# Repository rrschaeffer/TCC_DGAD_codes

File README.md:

# TCC_DGAD_codes
Repositório dos códigos utilizados - TCC Rafael R. Schaeffer - 2026/1

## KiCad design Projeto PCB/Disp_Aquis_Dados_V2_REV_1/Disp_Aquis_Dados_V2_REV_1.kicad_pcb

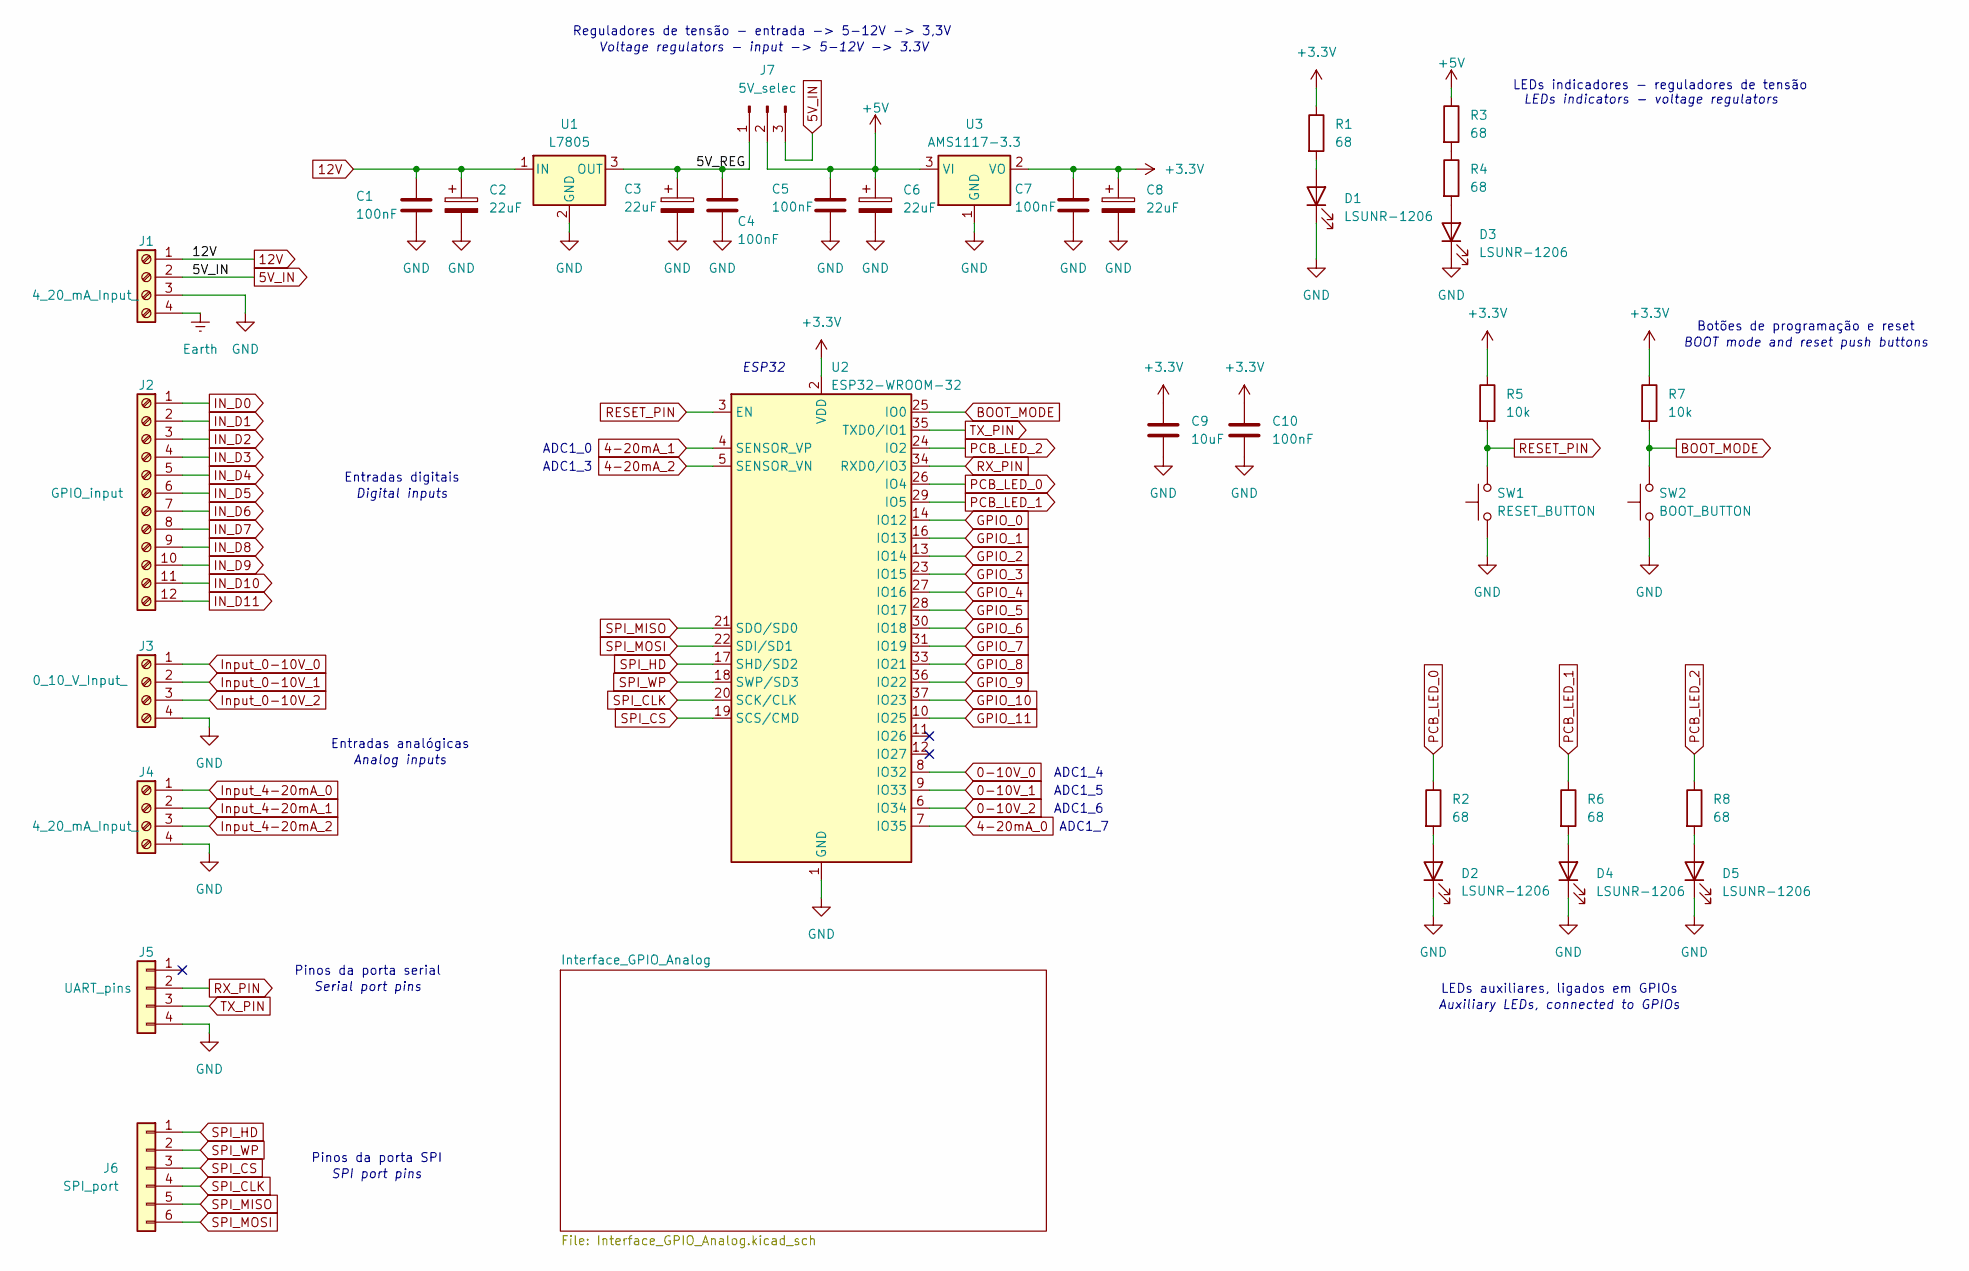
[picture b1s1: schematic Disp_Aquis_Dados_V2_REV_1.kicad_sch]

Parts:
C1, C4, C5, C7, C10: 100nF; C_0805_2012Metric_Pad1.18x1.45mm_HandSolder
C2, C3, C6, C8: 22uF; CP_Elec_5x5.3
C9: 10uF; C_0805_2012Metric_Pad1.18x1.45mm_HandSolder
D1, D2, D3, D4, D5: LSUNR-1206; LED_1206_3216Metric_Pad1.42x1.75mm_HandSolder
J1, J4: 4_20_mA_Input_; TerminalBlock_Phoenix_MKDS-1,5-4_1x04_P5.00mm_Horizontal
J2: GPIO_input; TerminalBlock_Phoenix_MKDS-1,5-12_1x12_P5.00mm_Horizontal
J3: 0_10_V_Input_; TerminalBlock_Phoenix_MKDS-1,5-4_1x04_P5.00mm_Horizontal
J5: UART_pins; PinHeader_1x04_P2.54mm_Vertical
J6: SPI_port; PinHeader_1x06_P2.54mm_Vertical
J7: 5V_selec; PinHeader_1x03_P2.54mm_Vertical
R1, R2, R3, R4, R6, R8: 68; R_1206_3216Metric_Pad1.30x1.75mm_HandSolder
R5, R7: 10k; R_1206_3216Metric_Pad1.30x1.75mm_HandSolder
SW1: RESET_BUTTON; SW_Push_1P1T_NO_6x6mm_H9.5mm
SW2: BOOT_BUTTON; SW_Push_1P1T_NO_6x6mm_H9.5mm
U1: L7805; TO-252-3_TabPin2
U2: ESP32-WROOM-32
U3: AMS1117-3.3; SOT-223

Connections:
0-10V_0: U2.8 (IO32); also elsewhere on the board
0-10V_1: U2.9 (IO33); also elsewhere on the board
0-10V_2: U2.6 (IO34); also elsewhere on the board
4-20mA_0: U2.7 (IO35); also elsewhere on the board
4-20mA_1: U2.4 (SENSOR_VP); also elsewhere on the board
4-20mA_2: U2.5 (SENSOR_VN); also elsewhere on the board
5V_IN: J1.2, J7.3
12V: C1.1, C2.1, J1.1, U1.1 (IN)
+3.3V: C7.1, C8.1, C9.1, C10.1, R1.1, R5.1, R7.1, U2.2 (VDD), U3.2 (VO); also elsewhere on the board
+5V: C5.1, C6.1, J7.2, R3.1, U3.3 (VI); also elsewhere on the board
/5V_REG: C3.1, C4.1, J7.1, U1.3 (OUT)
BOOT_MODE: R7.2, SW2.2, U2.25 (IO0)
Earth: J1.4
GND: C1.2, C2.2, C3.2, C4.2, C5.2, C6.2, C7.2, C8.2, C9.2, C10.2, D1.1 (K), D2.1 (K), D3.1 (K), D4.1 (K), D5.1 (K), J1.3, J3.4, J4.4, J5.4, SW1.1, SW2.1, U1.2 (GND), U2.1 (GND), U2.15 (GND), U2.38 (GND), U2.39 (GND), U3.1 (GND); also elsewhere on the board
GPIO_0: U2.14 (IO12); also elsewhere on the board
GPIO_1: U2.16 (IO13); also elsewhere on the board
GPIO_2: U2.13 (IO14); also elsewhere on the board
GPIO_3: U2.23 (IO15); also elsewhere on the board
GPIO_4: U2.27 (IO16); also elsewhere on the board
GPIO_5: U2.28 (IO17); also elsewhere on the board
GPIO_6: U2.30 (IO18); also elsewhere on the board
GPIO_7: U2.31 (IO19); also elsewhere on the board
GPIO_8: U2.33 (IO21); also elsewhere on the board
GPIO_9: U2.36 (IO22); also elsewhere on the board
GPIO_10: U2.37 (IO23); also elsewhere on the board
GPIO_11: U2.10 (IO25); also elsewhere on the board
IN_D0: J2.1; also elsewhere on the board
IN_D1: J2.2; also elsewhere on the board
IN_D2: J2.3; also elsewhere on the board
IN_D3: J2.4; also elsewhere on the board
IN_D4: J2.5; also elsewhere on the board
IN_D5: J2.6; also elsewhere on the board
IN_D6: J2.7; also elsewhere on the board
IN_D7: J2.8; also elsewhere on the board
IN_D8: J2.9; also elsewhere on the board
IN_D9: J2.10; also elsewhere on the board
IN_D10: J2.11; also elsewhere on the board
IN_D11: J2.12; also elsewhere on the board
Input_0-10V_0: J3.1; also elsewhere on the board
Input_0-10V_1: J3.2; also elsewhere on the board
Input_0-10V_2: J3.3; also elsewhere on the board
Input_4-20mA_0: J4.1; also elsewhere on the board
Input_4-20mA_1: J4.2; also elsewhere on the board
Input_4-20mA_2: J4.3; also elsewhere on the board
unnamed: D1.2 (A), R1.2
unnamed: D2.2 (A), R2.2
unnamed: D3.2 (A), R4.2
unnamed: D4.2 (A), R6.2
unnamed: D5.2 (A), R8.2
unnamed: R3.2, R4.1
PCB_LED_0: R2.1, U2.26 (IO4)
PCB_LED_1: R6.1, U2.29 (IO5)
PCB_LED_2: R8.1, U2.24 (IO2)
RESET_PIN: R5.2, SW1.2, U2.3 (EN)
RX_PIN: J5.2, U2.34 (RXD0/IO3)
SPI_CLK: J6.4, U2.20 (SCK/CLK)
SPI_CS: J6.3, U2.19 (SCS/CMD)
SPI_HD: J6.1, U2.17 (SHD/SD2)
SPI_MISO: J6.5, U2.21 (SDO/SD0)
SPI_MOSI: J6.6, U2.22 (SDI/SD1)
SPI_WP: J6.2, U2.18 (SWP/SD3)
TX_PIN: J5.3, U2.35 (TXD0/IO1)

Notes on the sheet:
LEDs indicators - voltage regulators
Pinos da porta serial
LEDs auxiliares, ligados em GPIOs
SPI port pins
Pinos da porta SPI
ADC1_7
ADC1_0
Digital inputs
ADC1_3
Auxiliary LEDs, connected to GPIOs
Entradas digitais
Voltage regulators - input -> 5-12V -> 3.3V
BOOT mode and reset push buttons
ESP32
Botões de programação e reset
ADC1_5
Analog inputs
ADC1_6
ADC1_4
Serial port pins
Reguladores de tensão - entrada -> 5-12V -> 3,3V
Entradas analógicas
LEDs indicadores - reguladores de tensão

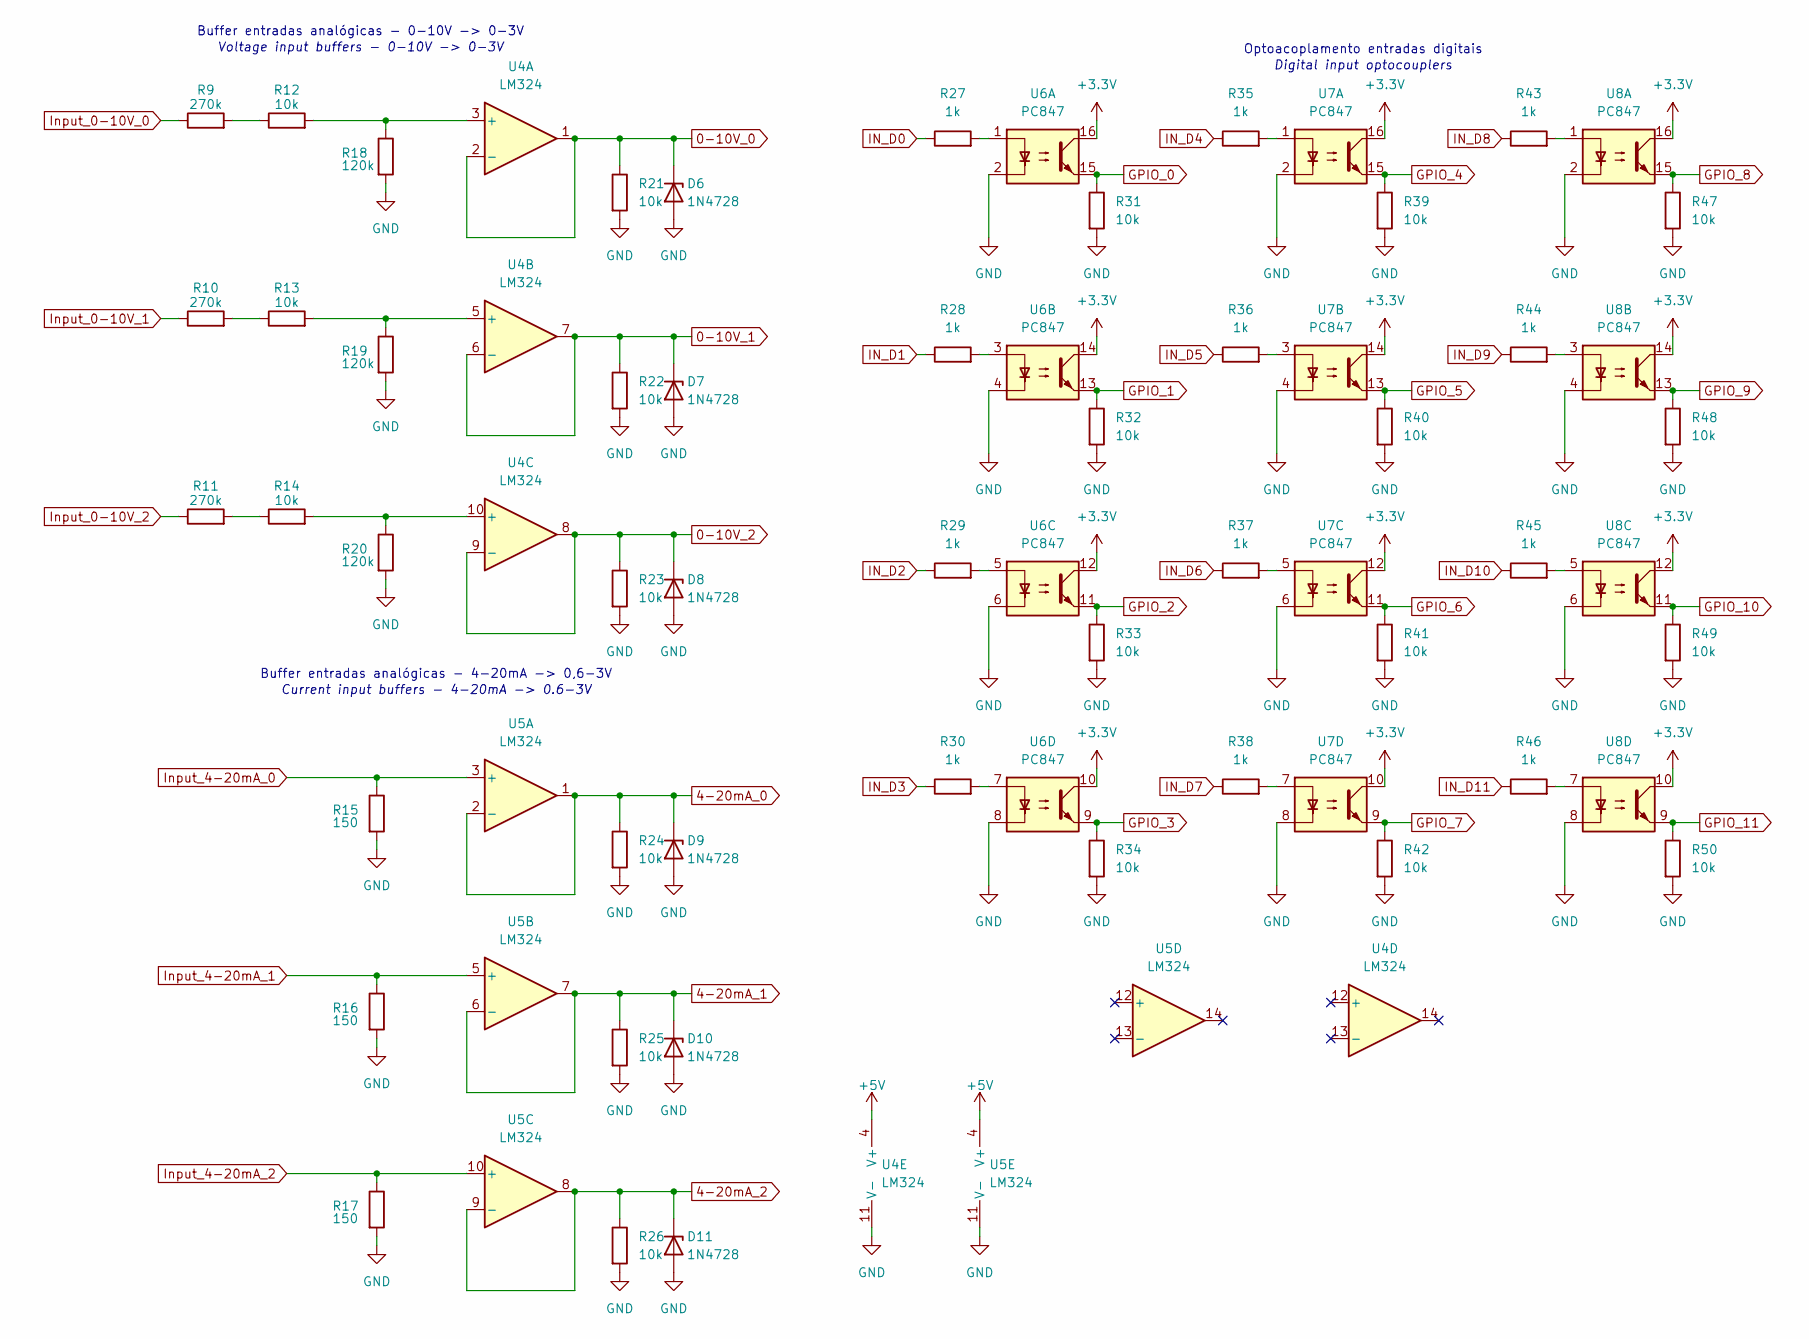
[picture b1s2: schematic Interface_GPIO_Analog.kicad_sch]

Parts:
D6, D7, D8, D9, D10, D11: 1N4728; D_DO-41_SOD81_P10.16mm_Horizontal
R9, R10, R11: 270k; R_1206_3216Metric_Pad1.30x1.75mm_HandSolder
R12, R13, R14, R21, R22, R23, R24, R25, R26, R31, R32, R33, R34, R39, R40, R41, R42, R47, R48, R49, R50: 10k; R_1206_3216Metric_Pad1.30x1.75mm_HandSolder
R15, R16, R17: 150; R_1206_3216Metric_Pad1.30x1.75mm_HandSolder
R18, R19, R20: 120k; R_1206_3216Metric_Pad1.30x1.75mm_HandSolder
R27, R28, R29, R30, R35, R36, R37, R38, R43, R44, R45, R46: 1k; R_2512_6332Metric_Pad1.40x3.35mm_HandSolder
U4, U5: LM324; SOIC-14_3.9x8.7mm_P1.27mm
U6, U7, U8: PC847; DIP-16_W7.62mm_Socket_LongPads

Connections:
0-10V_0: D6.1 (K), R21.1, U4.1, U4.2 (-); also elsewhere on the board
0-10V_1: D7.1 (K), R22.1, U4.6 (-), U4.7; also elsewhere on the board
0-10V_2: D8.1 (K), R23.1, U4.8, U4.9 (-); also elsewhere on the board
4-20mA_0: D9.1 (K), R24.1, U5.1, U5.2 (-); also elsewhere on the board
4-20mA_1: D10.1 (K), R25.1, U5.6 (-), U5.7; also elsewhere on the board
4-20mA_2: D11.1 (K), R26.1, U5.8, U5.9 (-); also elsewhere on the board
+3.3V: U6.10, U6.12, U6.14, U6.16, U7.10, U7.12, U7.14, U7.16, U8.10, U8.12, U8.14, U8.16; also elsewhere on the board
+5V: U4.4 (V+), U5.4 (V+); also elsewhere on the board
GND: D6.2 (A), D7.2 (A), D8.2 (A), D9.2 (A), D10.2 (A), D11.2 (A), R15.2, R16.2, R17.2, R18.2, R19.2, R20.2, R21.2, R22.2, R23.2, R24.2, R25.2, R26.2, R31.2, R32.2, R33.2, R34.2, R39.2, R40.2, R41.2, R42.2, R47.2, R48.2, R49.2, R50.2, U4.11 (V-), U5.11 (V-), U6.2, U6.4, U6.6, U6.8, U7.2, U7.4, U7.6, U7.8, U8.2, U8.4, U8.6, U8.8; also elsewhere on the board
GPIO_0: R31.1, U6.15; also elsewhere on the board
GPIO_1: R32.1, U6.13; also elsewhere on the board
GPIO_2: R33.1, U6.11; also elsewhere on the board
GPIO_3: R34.1, U6.9; also elsewhere on the board
GPIO_4: R39.1, U7.15; also elsewhere on the board
GPIO_5: R40.1, U7.13; also elsewhere on the board
GPIO_6: R41.1, U7.11; also elsewhere on the board
GPIO_7: R42.1, U7.9; also elsewhere on the board
GPIO_8: R47.1, U8.15; also elsewhere on the board
GPIO_9: R48.1, U8.13; also elsewhere on the board
GPIO_10: R49.1, U8.11; also elsewhere on the board
GPIO_11: R50.1, U8.9; also elsewhere on the board
IN_D0: R27.1; also elsewhere on the board
IN_D1: R28.1; also elsewhere on the board
IN_D2: R29.1; also elsewhere on the board
IN_D3: R30.1; also elsewhere on the board
IN_D4: R35.1; also elsewhere on the board
IN_D5: R36.1; also elsewhere on the board
IN_D6: R37.1; also elsewhere on the board
IN_D7: R38.1; also elsewhere on the board
IN_D8: R43.1; also elsewhere on the board
IN_D9: R44.1; also elsewhere on the board
IN_D10: R45.1; also elsewhere on the board
IN_D11: R46.1; also elsewhere on the board
Input_0-10V_0: R9.1; also elsewhere on the board
Input_0-10V_1: R10.1; also elsewhere on the board
Input_0-10V_2: R11.1; also elsewhere on the board
Input_4-20mA_0: R15.1, U5.3 (+); also elsewhere on the board
Input_4-20mA_1: R16.1, U5.5 (+); also elsewhere on the board
Input_4-20mA_2: R17.1, U5.10 (+); also elsewhere on the board
unnamed: R10.2, R13.1
unnamed: R11.2, R14.1
unnamed: R9.2, R12.1
unnamed: R27.2, U6.1
unnamed: R28.2, U6.3
unnamed: R29.2, U6.5
unnamed: R30.2, U6.7
unnamed: R35.2, U7.1
unnamed: R36.2, U7.3
unnamed: R37.2, U7.5
unnamed: R38.2, U7.7
unnamed: R43.2, U8.1
unnamed: R44.2, U8.3
unnamed: R45.2, U8.5
unnamed: R46.2, U8.7
unnamed: R12.2, R18.1, U4.3 (+)
unnamed: R13.2, R19.1, U4.5 (+)
unnamed: R14.2, R20.1, U4.10 (+)

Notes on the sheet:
Voltage input buffers - 0-10V -> 0-3V
Buffer entradas analógicas - 4-20mA -> 0,6-3V
Current input buffers - 4-20mA -> 0.6-3V
Digital input optocouplers
Optoacoplamento entradas digitais
Buffer entradas analógicas - 0-10V -> 0-3V

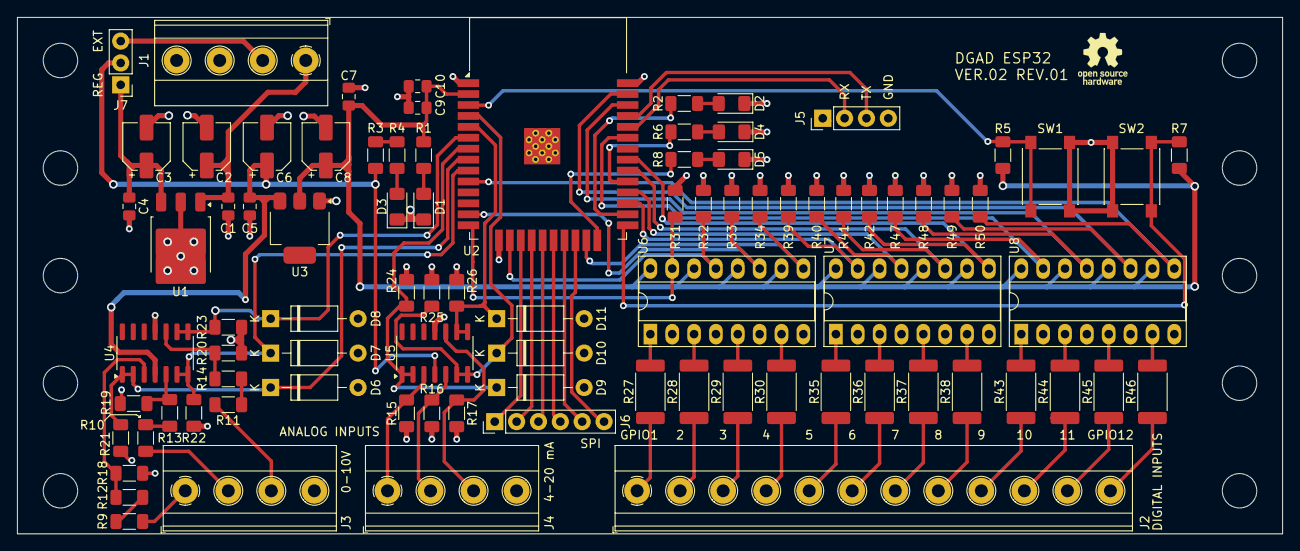
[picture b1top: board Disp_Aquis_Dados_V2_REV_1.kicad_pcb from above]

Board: 2 copper layers, 147.0 x 60.0 mm, 88 parts (0 on the bottom side), 79 nets.
